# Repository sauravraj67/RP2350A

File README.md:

# RP2350A

I made a custom RP2350A devboard  , it has a USB type C and i tried to keep the size of the board as small as possible and to have as much as useful pins available on the board..
<br>

<br>
## Overview
This project is a **compact 2-layer development board** based on the **Rp2350A**. It exposes **all usable GPIOs**, includes onboard **3.3V regulation**, and USB connectivity for easy programming and prototyping. 

## Features
- RP2350A Chip 
- 2-layer compact PCB
- USB connection for programming and power
- Onboard 3.3V voltage regulation

- ## Bill of Materials (BOM)
- 
| Qty | Description |  Total (USD) |
|----|-------------|-------------|
| 1 | PCB and Assembly  | 68.89  	 |
| 1 |Shipping JLCPCB - Discount  | 1.72 |

### 💰 Cost Summary
 
- **Estimated Total Cost:** **$70.61 USD**

## Schematic & PCB

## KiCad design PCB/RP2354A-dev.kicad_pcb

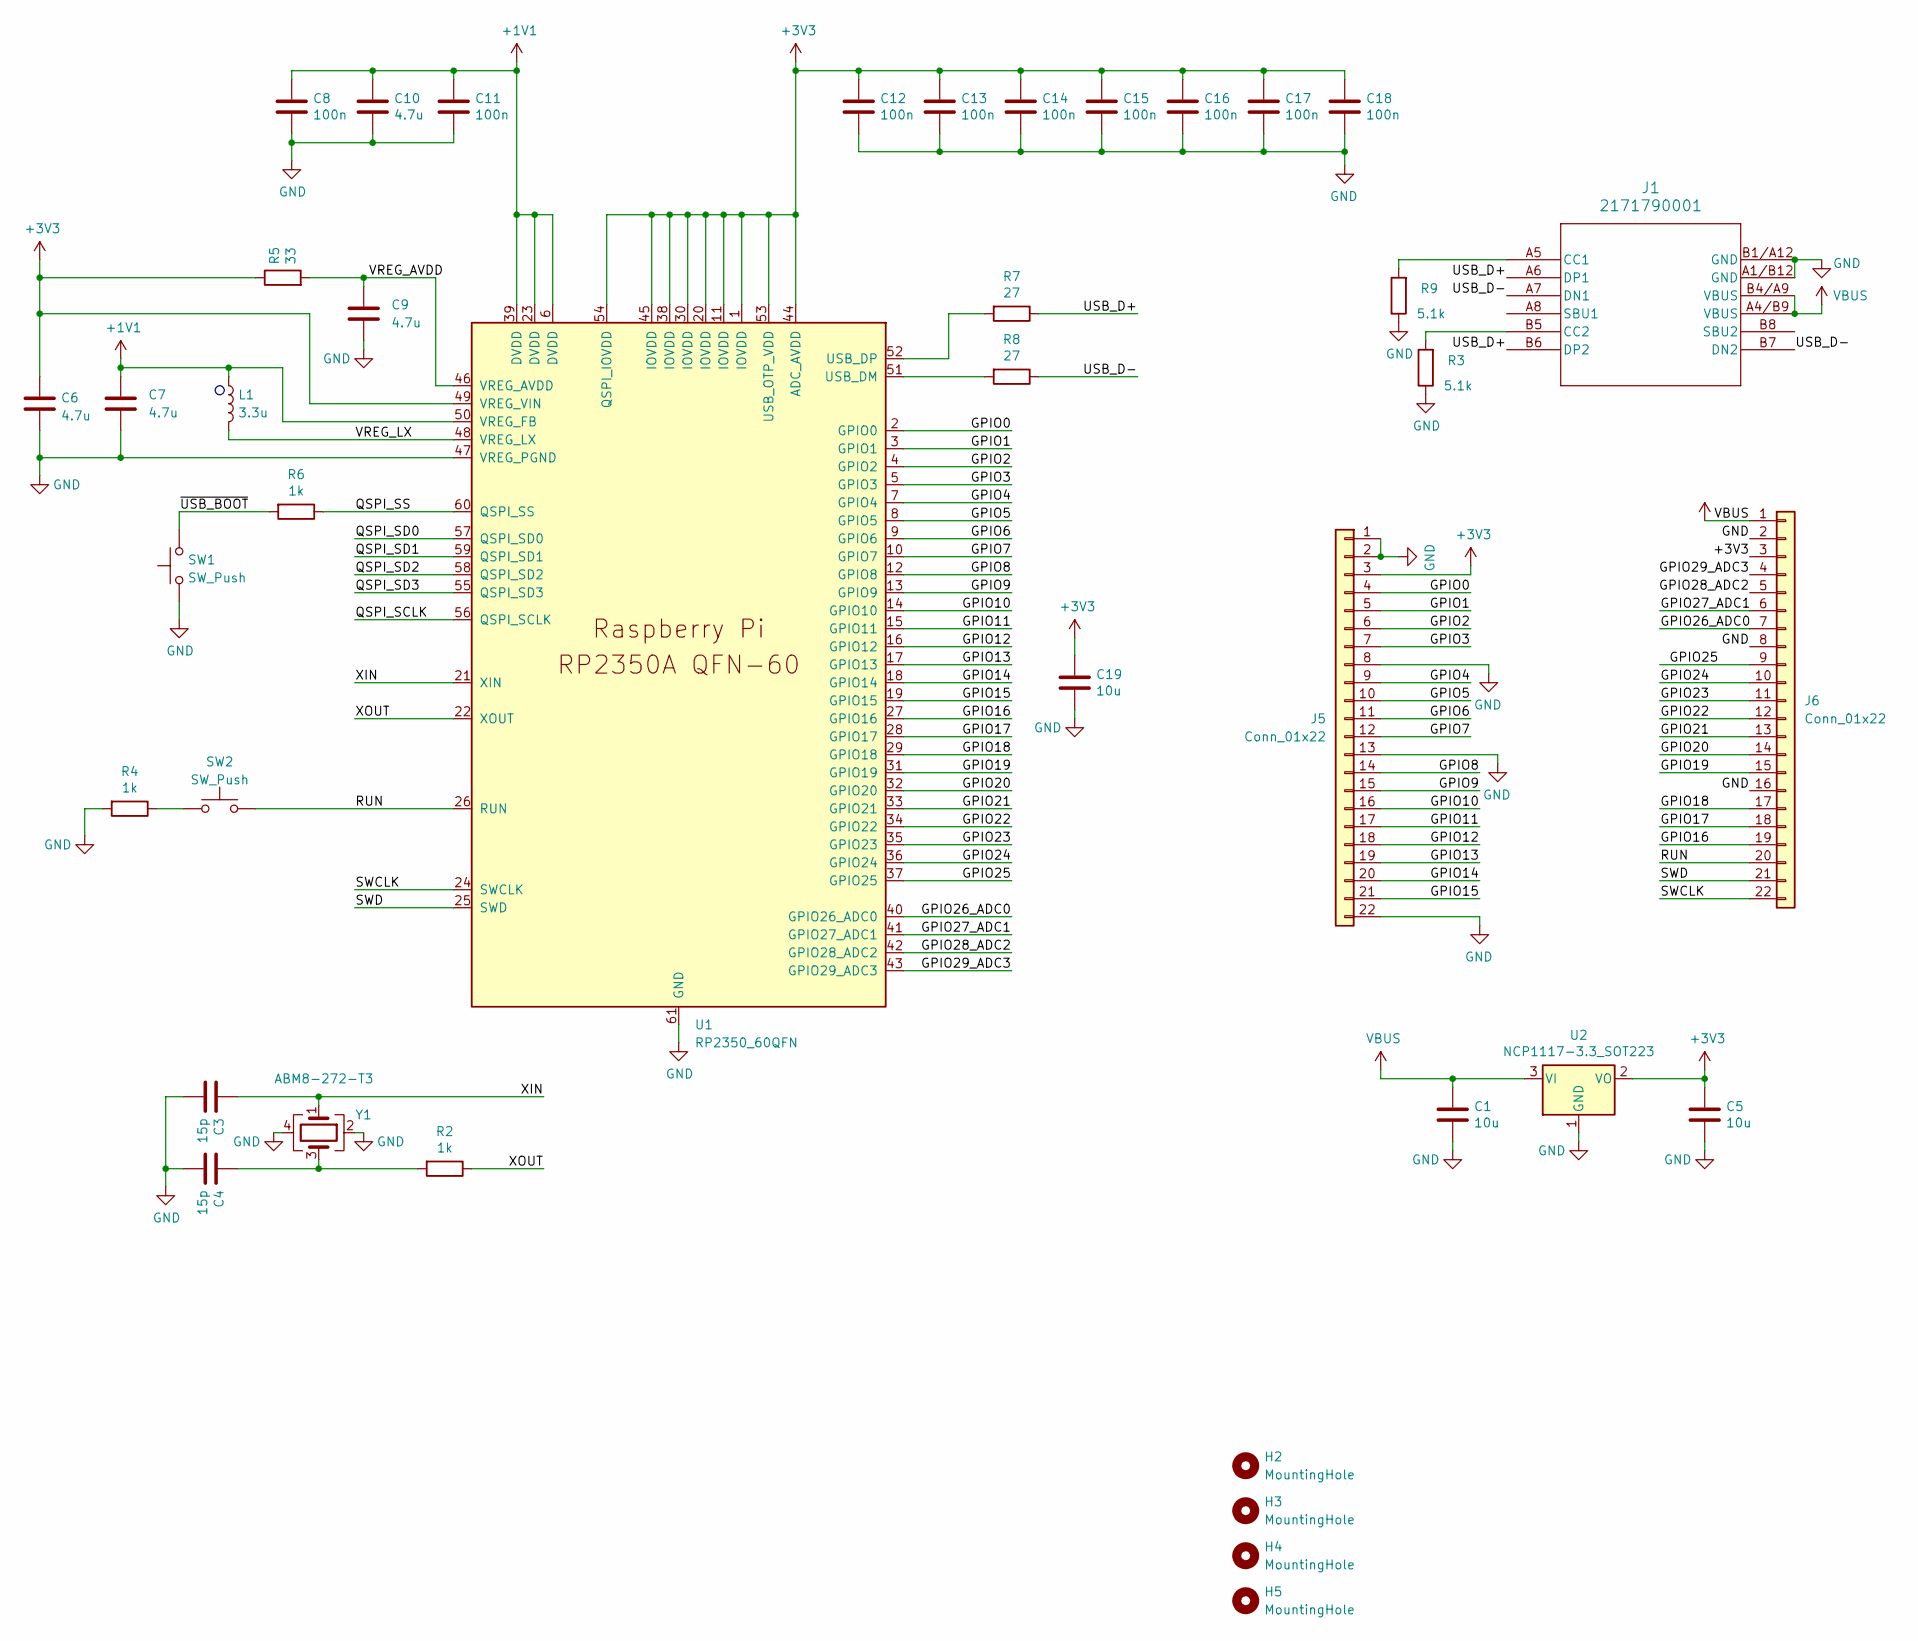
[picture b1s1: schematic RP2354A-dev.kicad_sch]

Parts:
C1, C5, C19: 10u; C_0805_2012Metric
C3, C4: 15p; C_0805_2012Metric
C6, C7, C9, C10: 4.7u; C_0805_2012Metric
C8, C11, C12, C13, C14, C15, C16, C17, C18: 100n; C_0805_2012Metric
H2, H3, H4, H5: MountingHole; MountingHole_3.2mm_M3
J1: 2171790001; 2171790001_MOL
J5, J6: Conn_01x22; PinHeader_1x22_P2.54mm_Vertical
L1: 3.3u; INDC2016X100N
R2, R4, R6: 1k; R_0805_2012Metric
R3, R9: 5.1k; R_0805_2012Metric
R5: 33; R_0805_2012Metric
R7, R8: 27; R_0805_2012Metric
SW1, SW2: SW_Push; Button_CnK_PTS636.0_6x3.5mm
U1: RP2350_60QFN; RP2350-QFN-60-1EP_7x7_P0.4mm_EP3.4x3.4mm_ThermalVias
U2: NCP1117-3.3_SOT223; SOT-223-3_TabPin2
Y1: ABM8-272-T3; Crystal_SMD_3225-4Pin_3.2x2.5mm

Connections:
+1V1: C7.1, C8.1, C10.1, C11.1, L1.1, U1.6 (DVDD), U1.23 (DVDD), U1.39 (DVDD), U1.50 (VREG_FB)
+3V3: C5.1, C6.1, C12.1, C13.1, C14.1, C15.1, C16.1, C17.1, C18.1, C19.1, J5.3, J6.3, R5.1, U1.1 (IOVDD), U1.11 (IOVDD), U1.20 (IOVDD), U1.30 (IOVDD), U1.38 (IOVDD), U1.44 (ADC_AVDD), U1.45 (IOVDD), U1.49 (VREG_VIN), U1.53 (USB_OTP_VDD), U1.54 (QSPI_IOVDD), U2.2 (VO)
/GPIO0: J5.4, U1.2 (GPIO0)
/GPIO1: J5.5, U1.3 (GPIO1)
/GPIO2: J5.6, U1.4 (GPIO2)
/GPIO3: J5.7, U1.5 (GPIO3)
/GPIO4: J5.9, U1.7 (GPIO4)
/GPIO5: J5.10, U1.8 (GPIO5)
/GPIO6: J5.11, U1.9 (GPIO6)
/GPIO7: J5.12, U1.10 (GPIO7)
/GPIO8: J5.14, U1.12 (GPIO8)
/GPIO9: J5.15, U1.13 (GPIO9)
/GPIO10: J5.16, U1.14 (GPIO10)
/GPIO11: J5.17, U1.15 (GPIO11)
/GPIO12: J5.18, U1.16 (GPIO12)
/GPIO13: J5.19, U1.17 (GPIO13)
/GPIO14: J5.20, U1.18 (GPIO14)
/GPIO15: J5.21, U1.19 (GPIO15)
/GPIO16: J6.19, U1.27 (GPIO16)
/GPIO17: J6.18, U1.28 (GPIO17)
/GPIO18: J6.17, U1.29 (GPIO18)
/GPIO19: J6.15, U1.31 (GPIO19)
/GPIO20: J6.14, U1.32 (GPIO20)
/GPIO21: J6.13, U1.33 (GPIO21)
/GPIO22: J6.12, U1.34 (GPIO22)
/GPIO23: J6.11, U1.35 (GPIO23)
/GPIO24: J6.10, U1.36 (GPIO24)
/GPIO25: J6.9, U1.37 (GPIO25)
/GPIO26_ADC0: J6.7, U1.40 (GPIO26_ADC0)
/GPIO27_ADC1: J6.6, U1.41 (GPIO27_ADC1)
/GPIO28_ADC2: J6.5, U1.42 (GPIO28_ADC2)
/GPIO29_ADC3: J6.4, U1.43 (GPIO29_ADC3)
/QSPI_SCLK: U1.56 (QSPI_SCLK)
/QSPI_SD0: U1.57 (QSPI_SD0)
/QSPI_SD1: U1.59 (QSPI_SD1)
/QSPI_SD2: U1.58 (QSPI_SD2)
/QSPI_SD3: U1.55 (QSPI_SD3)
/QSPI_SS: R6.1, U1.60 (QSPI_SS)
/RUN: J6.20, SW2.2, U1.26 (RUN)
/SWCLK: J6.22, U1.24 (SWCLK)
/SWD: J6.21, U1.25 (SWD)
/USB_D+: J1.A6 (DP1), J1.B6 (DP2), R7.1
/USB_D-: J1.A7 (DN1), J1.B7 (DN2), R8.1
/VREG_AVDD: C9.1, R5.2, U1.46 (VREG_AVDD)
/VREG_LX: L1.2, U1.48 (VREG_LX)
/XIN: C3.1, U1.21 (XIN), Y1.1
/XOUT: R2.1, U1.22 (XOUT)
/~USB_BOOT: R6.2, SW1.2
GND: C1.2, C3.2, C4.2, C5.2, C6.2, C7.2, C8.2, C9.2, C10.2, C11.2, C12.2, C13.2, C14.2, C15.2, C16.2, C17.2, C18.2, C19.2, J1.A1/B12 (GND), J1.B1/A12 (GND), J5.1, J5.2, J5.8, J5.13, J5.22, J6.2, J6.8, J6.16, R3.1, R4.2, R9.1, SW1.1, U1.47 (VREG_PGND), U1.61 (GND), U2.1 (GND), Y1.2, Y1.4
unnamed: C4.1, R2.2, Y1.3
unnamed: J1.A5 (CC1), R9.2
unnamed: J1.B5 (CC2), R3.2
unnamed: R4.1, SW2.1
unnamed: R8.2, U1.51 (USB_DM)
unnamed: R7.2, U1.52 (USB_DP)
VBUS: C1.1, J1.A4/B9 (VBUS), J1.B4/A9 (VBUS), J6.1, U2.3 (VI)

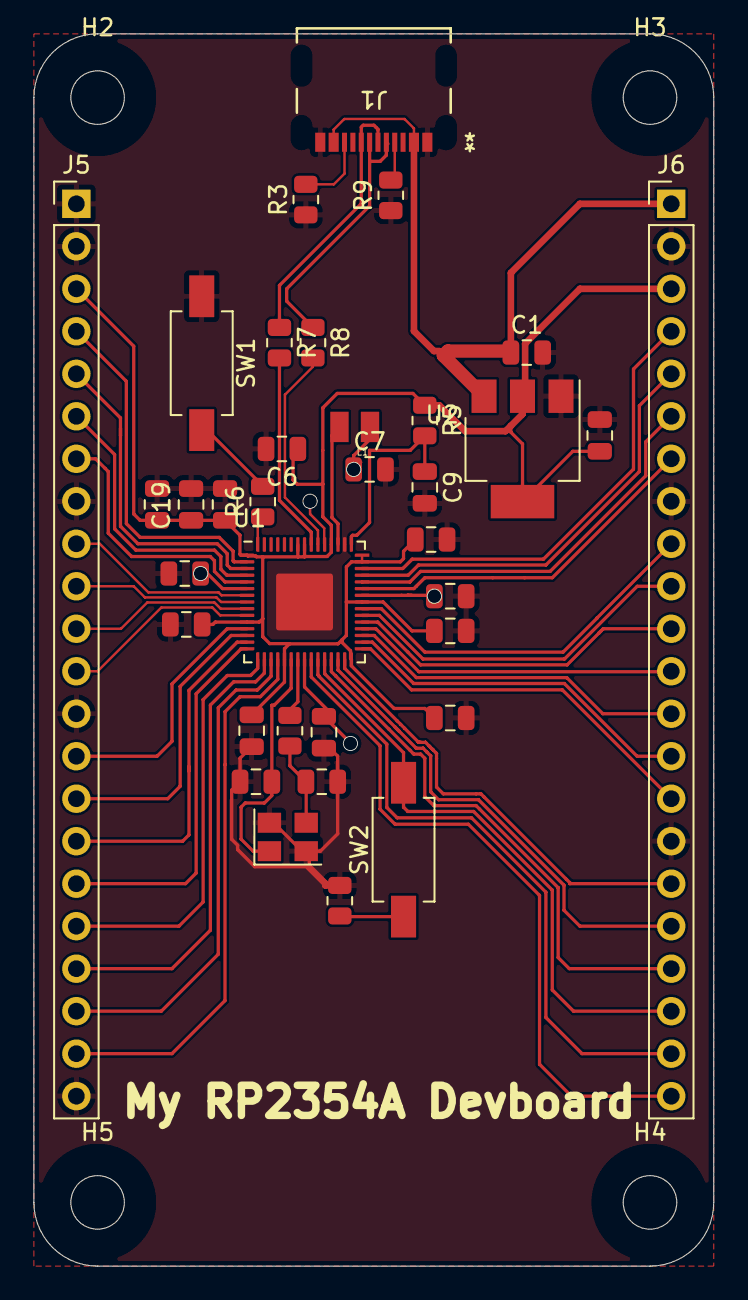
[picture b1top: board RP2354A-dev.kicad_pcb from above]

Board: 2 copper layers, 40.6 x 73.7 mm, 39 parts (0 on the bottom side), 51 nets.

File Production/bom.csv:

Designator,Footprint,Quantity,Value,LCSC Part #
"C1, C19, C5",0805,3,10u,
"C10, C6, C7, C9",0805,4,4.7u,
"C11, C12, C13, C14, C15, C16, C17, C18, C8",0805,9,100n,
"C3, C4",0805,2,15p,
J1,2171790001_MOL,1,2171790001,
"J5, J6",PinHeader_1x22_P2.54mm_Vertical,2,Conn_01x22,
L1,INDC2016X100N,1,3.3u,
"R2, R4, R6",0805,3,1k,
"R3, R9",0805,2,5.1k,
R5,0805,1,33,
"R7, R8",0805,2,27,
"SW1, SW2",Button_CnK_PTS636.0_6x3.5mm,2,SW_Push,
U1,RP2350-QFN-60-1EP_7x7_P0.4mm_EP3.4x3.4mm_ThermalVias,1,RP2350_60QFN,
U2,SOT-223-3_TabPin2,1,NCP1117-3.3_SOT223,
Y1,Crystal_SMD_3225-4Pin_3.2x2.5mm,1,ABM8-272-T3,
